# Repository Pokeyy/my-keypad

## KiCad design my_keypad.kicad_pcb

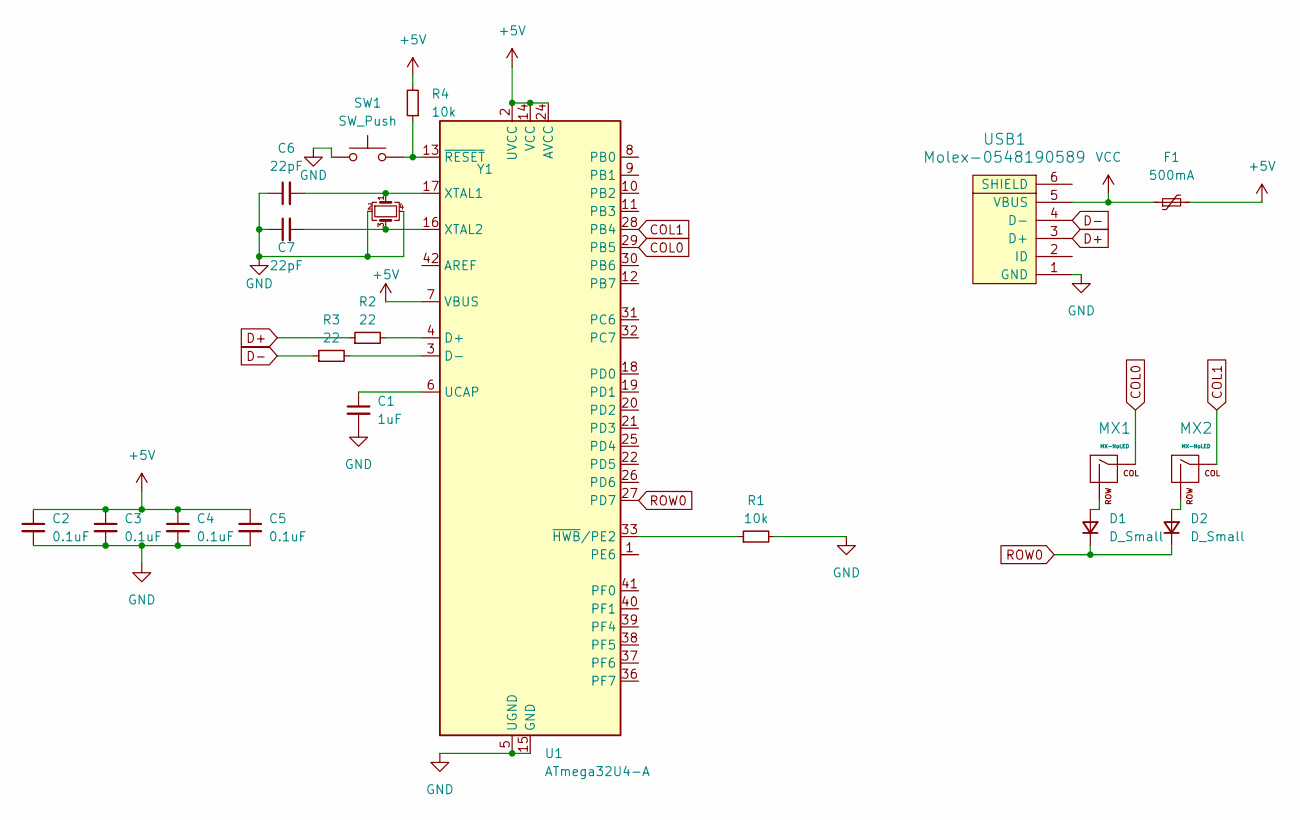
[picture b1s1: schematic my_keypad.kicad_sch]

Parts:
C1: 1uF; C_0805_2012Metric
C2, C3, C4, C5: 0.1uF; C_0805_2012Metric
C6, C7: 22pF; C_0805_2012Metric
D1, D2: D_Small; D_SOD-123
F1: 500mA; Fuse_1206_3216Metric
MX1, MX2: MX-NoLED; MX-1U-NoLED
R1, R4: 10k; R_0805_2012Metric
R2, R3: 22; R_0805_2012Metric
SW1: SW_Push; SKQG-1155865
U1: ATmega32U4-A; TQFP-44_10x10mm_P0.8mm
USB1: Molex-0548190589
Y1: Crystal_GND24_Small; Crystal_SMD_3225-4Pin_3.2x2.5mm

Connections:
+5V: C2.1, C3.1, C4.1, C5.1, F1.2, R4.2, U1.2 (UVCC), U1.7 (VBUS), U1.14 (VCC), U1.24 (AVCC), U1.34 (VCC), U1.44 (AVCC)
COL0: MX1.1 (COL), U1.29 (PB5)
COL1: MX2.1 (COL), U1.28 (PB4)
D+: R2.1, USB1.3 (D+)
D-: R3.1, USB1.4 (D-)
GND: C1.2, C2.2, C3.2, C4.2, C5.2, C6.1, C7.1, R1.2, SW1.1, U1.5 (UGND), U1.15 (GND), U1.23 (GND), U1.35 (GND), U1.43 (GND), USB1.1 (GND), Y1.2, Y1.4
unnamed: D1.2 (A), MX1.2 (ROW)
unnamed: D2.2 (A), MX2.2 (ROW)
unnamed: R2.2, U1.4 (D+)
unnamed: R3.2, U1.3 (D-)
unnamed: C1.1, U1.6 (UCAP)
unnamed: C6.2, U1.17 (XTAL1), Y1.1
unnamed: C7.2, U1.16 (XTAL2), Y1.3
unnamed: R1.1, U1.33 (~HWB/PE2)
unnamed: R4.1, SW1.2, U1.13 (~RESET)
ROW0: D1.1 (K), D2.1 (K), U1.27 (PD7)
VCC: F1.1, USB1.5 (VBUS)

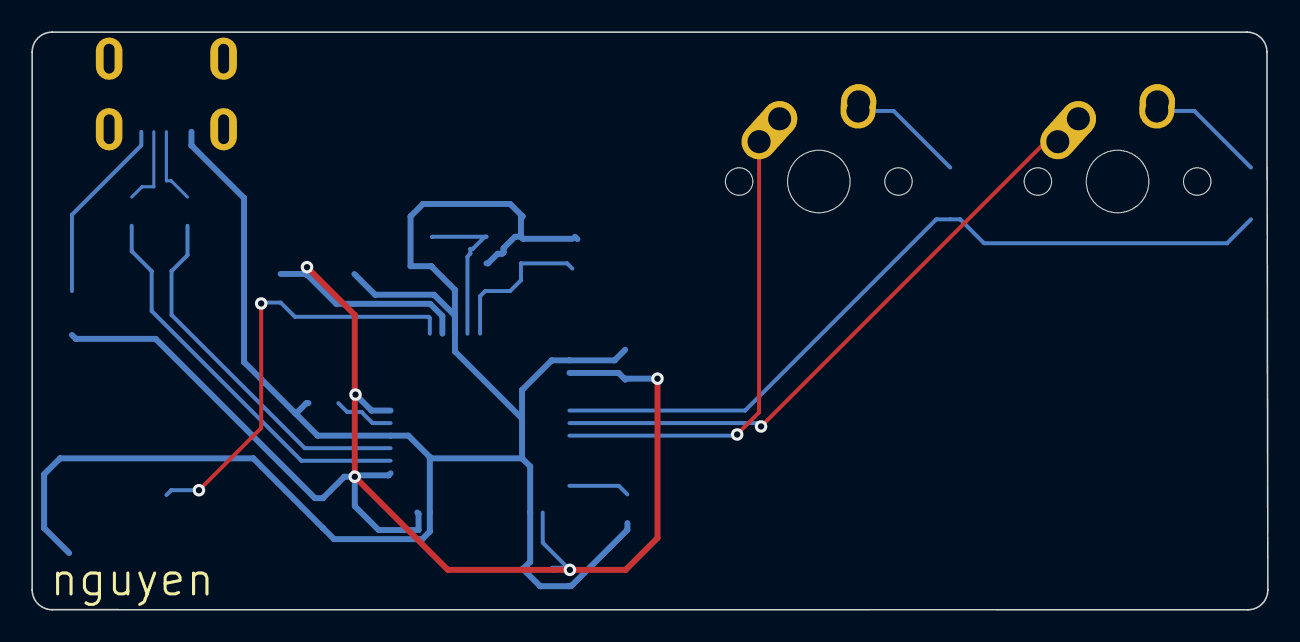
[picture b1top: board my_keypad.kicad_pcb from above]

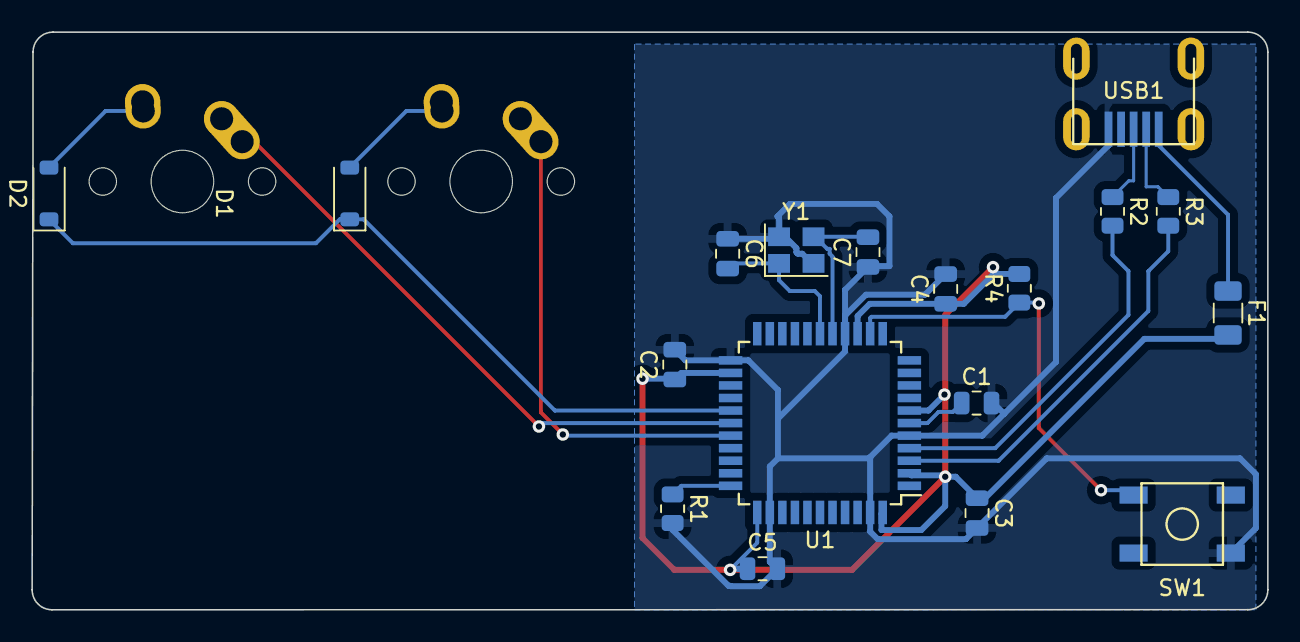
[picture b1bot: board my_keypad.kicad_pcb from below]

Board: 2 copper layers, 78.8 x 36.8 mm, 20 parts (18 on the bottom side), 17 nets.

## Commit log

2023-07-07 initialize project (new repo)
2023-07-07 submodule libs
2023-07-07 finish footprints/sch
2023-07-07 placed pcb comps
2023-07-09 routing finished
2023-07-09 added ground fill
2023-07-09 fixed errors
